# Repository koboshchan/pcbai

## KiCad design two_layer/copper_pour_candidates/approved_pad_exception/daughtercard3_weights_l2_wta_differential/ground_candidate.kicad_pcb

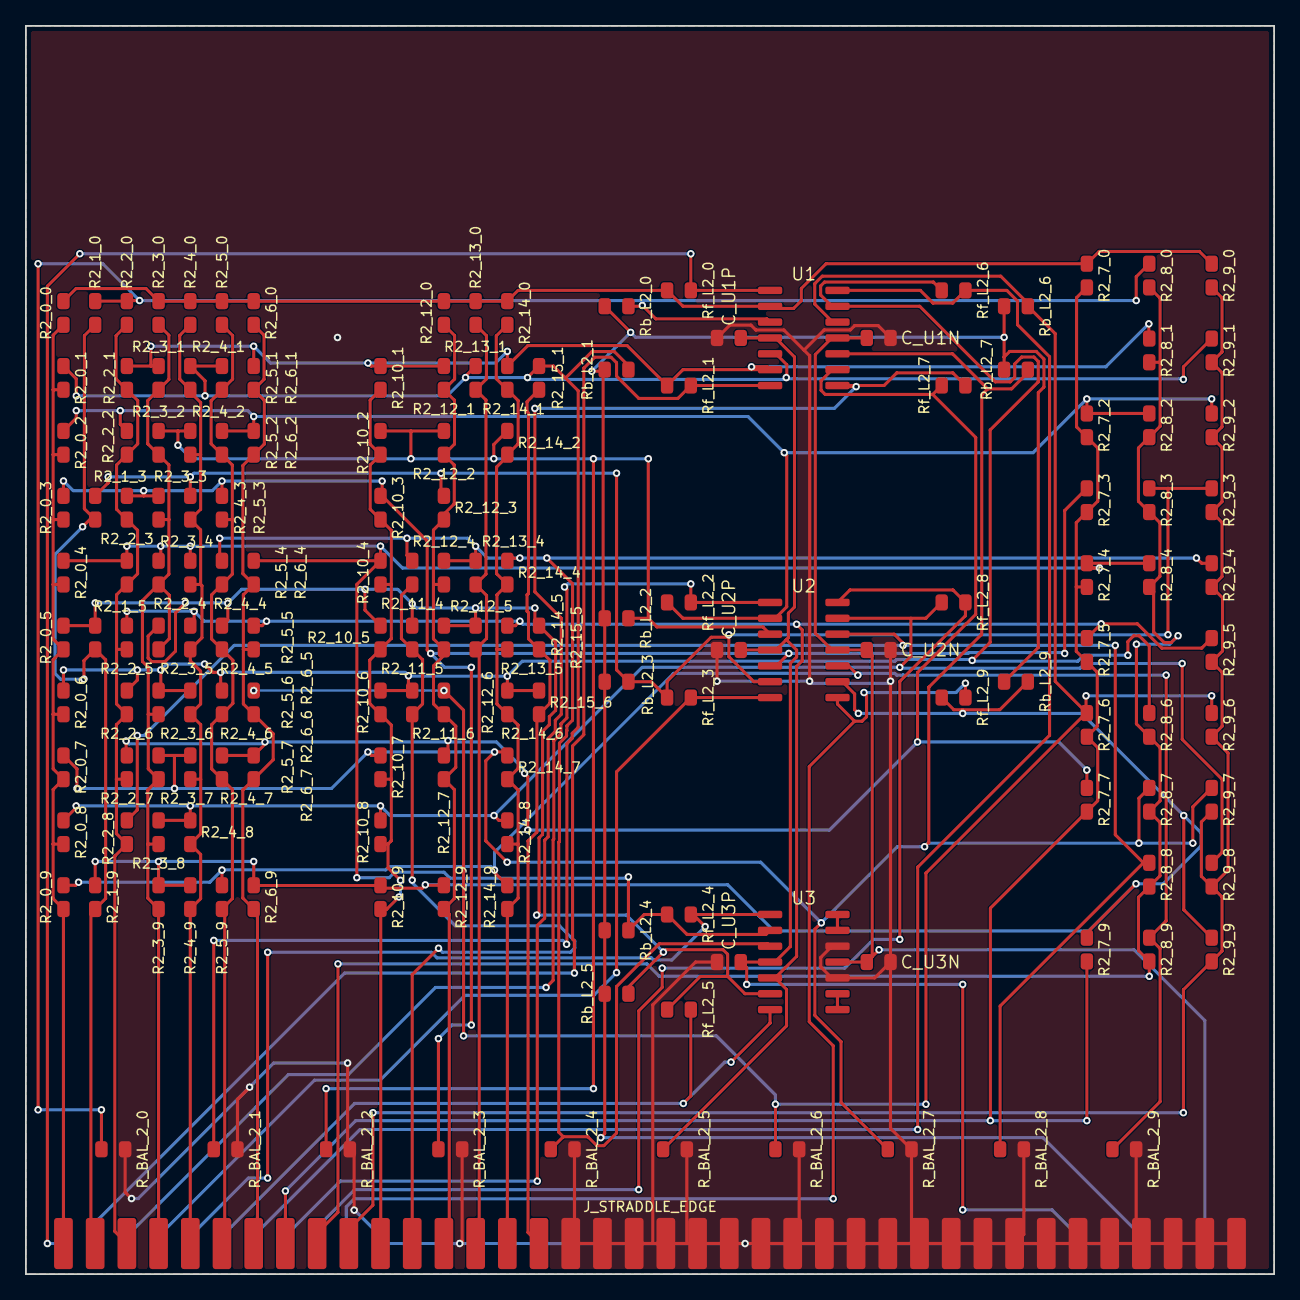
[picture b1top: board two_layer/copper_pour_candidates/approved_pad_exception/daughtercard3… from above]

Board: 2 copper layers, 100.0 x 100.0 mm, 163 parts (0 on the bottom side), 52 nets.

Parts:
C_U1N, C_U1P, C_U2N, C_U2P, C_U3N, C_U3P: 0.1uF; C_0805_2012Metric
J_STRADDLE_EDGE: PinHeader_2x38_Straddle; PinHeader_2x38_Straddle_P2.54mm
R2_0_0, R2_3_2, R2_8_3, R2_9_1, R2_10_6: 91k; R_0805_2012Metric
R2_0_1, R2_3_0, R2_6_5, R2_7_4, R2_9_0, R2_14_1: 100k; R_0805_2012Metric
R2_0_2: 1.6M; R_0805_2012Metric
R2_0_3, R2_1_3, R2_5_4, R2_6_2, R2_7_6, R2_10_5, R2_10_8, R2_13_0, R2_14_0: 220k; R_0805_2012Metric
R2_0_4, R2_2_7, R2_5_3, R2_7_3, R2_8_6, R2_9_3, R2_13_5: 270k; R_0805_2012Metric
R2_0_5, R2_0_6, R2_5_0: 56k; R_0805_2012Metric
R2_0_7, R2_3_5: 470k; R_0805_2012Metric
R2_0_8, R2_1_9, R2_5_5, R2_5_9, R2_9_2, R2_9_4, R2_9_8, R2_10_7, R2_11_4, R2_11_6, R2_12_6: 180k; R_0805_2012Metric
R2_0_9, R2_2_2, R2_4_5, R2_4_6, R2_8_9, R2_12_5, R2_14_9: 300k; R_0805_2012Metric
R2_1_0, R2_2_3, R2_2_4, R2_8_0, R2_10_3, R2_11_5, R2_14_7, R2_15_5: 240k; R_0805_2012Metric
R2_1_5, R2_5_1: 82k; R_0805_2012Metric
R2_2_0, R2_10_9, R2_14_8: 110k; R_0805_2012Metric
R2_2_1: 51k; R_0805_2012Metric
R2_2_5, R2_3_3, R2_3_7, R2_15_6: 360k; R_0805_2012Metric
R2_2_6, R2_4_9: 430k; R_0805_2012Metric
R2_2_8: 5.1M; R_0805_2012Metric
R2_3_1, R2_6_9, R2_7_7, R2_9_9, R2_10_2, R2_13_4: 150k; R_0805_2012Metric
R2_3_4, R2_3_9, R2_5_2, R2_14_4: 130k; R_0805_2012Metric
R2_3_6, R2_5_6, R2_6_4, R2_7_2, R2_7_5, R2_10_1: 68k; R_0805_2012Metric
R2_3_8, R2_5_7, R2_6_0, R2_6_6, R2_8_2, R2_12_1, R2_12_4, R2_14_6: 200k; R_0805_2012Metric
R2_4_0, R2_9_5: 1M; R_0805_2012Metric
R2_4_1, R2_4_4, R2_8_8: 120k; R_0805_2012Metric
R2_4_2: 680k; R_0805_2012Metric
R2_4_3, R2_14_2: 750k; R_0805_2012Metric
R2_4_7, R2_12_3: 390k; R_0805_2012Metric
R2_4_8: 62k; R_0805_2012Metric
R2_6_1, R2_12_7: 43k; R_0805_2012Metric
R2_6_7, R2_8_7: 330k; R_0805_2012Metric
R2_7_0, R2_7_9: 75k; R_0805_2012Metric
R2_8_1, R2_12_9, R2_15_1: 160k; R_0805_2012Metric
R2_8_4, R2_9_6, R2_9_7: 620k; R_0805_2012Metric
R2_10_4: 33k; R_0805_2012Metric
R2_12_0: 510k; R_0805_2012Metric
R2_12_2: 1.1M; R_0805_2012Metric
R2_13_1: 820k; R_0805_2012Metric
R2_14_5: 2.7M; R_0805_2012Metric
R_BAL_2_0: 14.7k; R_0805_2012Metric
R_BAL_2_1: 24.9k; R_0805_2012Metric
R_BAL_2_2: 35.7k; R_0805_2012Metric
R_BAL_2_3: 61.9k; R_0805_2012Metric
R_BAL_2_4: 17.4k; R_0805_2012Metric
R_BAL_2_5: 28k; R_0805_2012Metric
R_BAL_2_6: 14.3k; R_0805_2012Metric
R_BAL_2_7: 34k; R_0805_2012Metric
R_BAL_2_8: 21k; R_0805_2012Metric
R_BAL_2_9: 18.2k; R_0805_2012Metric
Rb_L2_0: 270k; R_0805_2012Metric
Rb_L2_1, Rb_L2_3: 160k; R_0805_2012Metric
Rb_L2_2, Rb_L2_4: 560k; R_0805_2012Metric
Rb_L2_5: 2M; R_0805_2012Metric
Rb_L2_6: 240k; R_0805_2012Metric
Rb_L2_7: 3.9M; R_0805_2012Metric
Rb_L2_9: 360k; R_0805_2012Metric
Rf_L2_0, Rf_L2_1, Rf_L2_2, Rf_L2_3, Rf_L2_4, Rf_L2_5, Rf_L2_6, Rf_L2_7, Rf_L2_8, Rf_L2_9: 100k; R_0805_2012Metric
U1, U2, U3: TL074; SOIC-14_3.9x8.7mm_P1.27mm

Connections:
+5V_REF: J_STRADDLE_EDGE.B35, Rb_L2_0.1, Rb_L2_1.1, Rb_L2_2.1, Rb_L2_3.1, Rb_L2_4.1, Rb_L2_5.1, Rb_L2_6.1, Rb_L2_7.1, Rb_L2_9.1
+15V: C_U1P.2, C_U2P.2, C_U3P.2, J_STRADDLE_EDGE.B33, J_STRADDLE_EDGE.B34, U1.4, U2.4, U3.4
-15V: C_U1N.1, C_U2N.1, C_U3N.1, J_STRADDLE_EDGE.B37, J_STRADDLE_EDGE.B38, U1.11, U2.11, U3.11
ACT_0: J_STRADDLE_EDGE.A1, R2_0_0.1, R2_0_1.1, R2_0_2.1, R2_0_3.1, R2_0_4.1, R2_0_5.1, R2_0_6.1, R2_0_7.1, R2_0_8.1, R2_0_9.1
ACT_1: J_STRADDLE_EDGE.A2, R2_1_0.1, R2_1_3.1, R2_1_5.1, R2_1_9.1
ACT_2: J_STRADDLE_EDGE.A3, R2_2_0.1, R2_2_1.1, R2_2_2.1, R2_2_3.1, R2_2_4.1, R2_2_5.1, R2_2_6.1, R2_2_7.1, R2_2_8.1
ACT_3: J_STRADDLE_EDGE.A4, R2_3_0.1, R2_3_1.1, R2_3_2.1, R2_3_3.1, R2_3_4.1, R2_3_5.1, R2_3_6.1, R2_3_7.1, R2_3_8.1, R2_3_9.1
ACT_4: J_STRADDLE_EDGE.A5, R2_4_0.1, R2_4_1.1, R2_4_2.1, R2_4_3.1, R2_4_4.1, R2_4_5.1, R2_4_6.1, R2_4_7.1, R2_4_8.1, R2_4_9.1
ACT_5: J_STRADDLE_EDGE.A6, R2_5_0.1, R2_5_1.1, R2_5_2.1, R2_5_3.1, R2_5_4.1, R2_5_5.1, R2_5_6.1, R2_5_7.1, R2_5_9.1
ACT_6: J_STRADDLE_EDGE.A7, R2_6_0.1, R2_6_1.1, R2_6_2.1, R2_6_4.1, R2_6_5.1, R2_6_6.1, R2_6_7.1, R2_6_9.1
ACT_7: J_STRADDLE_EDGE.A8, R2_7_0.1, R2_7_2.1, R2_7_3.1, R2_7_4.1, R2_7_5.1, R2_7_6.1, R2_7_7.1, R2_7_9.1
ACT_8: J_STRADDLE_EDGE.A9, R2_8_0.1, R2_8_1.1, R2_8_2.1, R2_8_3.1, R2_8_4.1, R2_8_6.1, R2_8_7.1, R2_8_8.1, R2_8_9.1
ACT_9: J_STRADDLE_EDGE.A10, R2_9_0.1, R2_9_1.1, R2_9_2.1, R2_9_3.1, R2_9_4.1, R2_9_5.1, R2_9_6.1, R2_9_7.1, R2_9_8.1, R2_9_9.1
ACT_10: J_STRADDLE_EDGE.A11, R2_10_1.1, R2_10_2.1, R2_10_3.1, R2_10_4.1, R2_10_5.1, R2_10_6.1, R2_10_7.1, R2_10_8.1, R2_10_9.1
ACT_11: J_STRADDLE_EDGE.A12, R2_11_4.1, R2_11_5.1, R2_11_6.1
ACT_12: J_STRADDLE_EDGE.A13, R2_12_0.1, R2_12_1.1, R2_12_2.1, R2_12_3.1, R2_12_4.1, R2_12_5.1, R2_12_6.1, R2_12_7.1, R2_12_9.1
ACT_13: J_STRADDLE_EDGE.A14, R2_13_0.1, R2_13_1.1, R2_13_4.1, R2_13_5.1
ACT_14: J_STRADDLE_EDGE.A15, R2_14_0.1, R2_14_1.1, R2_14_2.1, R2_14_4.1, R2_14_5.1, R2_14_6.1, R2_14_7.1, R2_14_8.1, R2_14_9.1
ACT_15: J_STRADDLE_EDGE.A16, R2_15_1.1, R2_15_5.1, R2_15_6.1
GND: C_U1N.2, C_U1P.1, C_U2N.2, C_U2P.1, C_U3N.2, C_U3P.1, J_STRADDLE_EDGE.A17, J_STRADDLE_EDGE.A18, J_STRADDLE_EDGE.A19, J_STRADDLE_EDGE.A20, J_STRADDLE_EDGE.A21, J_STRADDLE_EDGE.A22, J_STRADDLE_EDGE.A23, J_STRADDLE_EDGE.A24, J_STRADDLE_EDGE.A25, J_STRADDLE_EDGE.A26, J_STRADDLE_EDGE.A27, J_STRADDLE_EDGE.A28, J_STRADDLE_EDGE.A29, J_STRADDLE_EDGE.A30, J_STRADDLE_EDGE.A31, J_STRADDLE_EDGE.A32, J_STRADDLE_EDGE.A33, J_STRADDLE_EDGE.A34, J_STRADDLE_EDGE.A35, J_STRADDLE_EDGE.A36, J_STRADDLE_EDGE.A37, J_STRADDLE_EDGE.A38, J_STRADDLE_EDGE.B11, J_STRADDLE_EDGE.B12, J_STRADDLE_EDGE.B13, J_STRADDLE_EDGE.B14, J_STRADDLE_EDGE.B15, J_STRADDLE_EDGE.B16, J_STRADDLE_EDGE.B17, J_STRADDLE_EDGE.B18, J_STRADDLE_EDGE.B19, J_STRADDLE_EDGE.B20, J_STRADDLE_EDGE.B21, J_STRADDLE_EDGE.B22, J_STRADDLE_EDGE.B23, J_STRADDLE_EDGE.B24, J_STRADDLE_EDGE.B25, J_STRADDLE_EDGE.B26, J_STRADDLE_EDGE.B27, J_STRADDLE_EDGE.B28, J_STRADDLE_EDGE.B29, J_STRADDLE_EDGE.B30, J_STRADDLE_EDGE.B31, J_STRADDLE_EDGE.B32, R_BAL_2_0.2, R_BAL_2_1.2, R_BAL_2_2.2, R_BAL_2_3.2, R_BAL_2_4.2, R_BAL_2_5.2, R_BAL_2_6.2, R_BAL_2_7.2, R_BAL_2_8.2, R_BAL_2_9.2, U3.10, U3.12
INV_L2_0: R2_0_0.2, R2_3_0.2, R2_4_0.2, R2_5_0.2, R2_6_0.2, R2_7_0.2, R2_9_0.2, R2_12_0.2, R2_13_0.2, R2_14_0.2, Rf_L2_0.1, U1.2
INV_L2_1: R2_2_1.2, R2_3_1.2, R2_6_1.2, R2_8_1.2, R2_10_1.2, R2_12_1.2, R2_14_1.2, Rf_L2_1.1, U1.6
INV_L2_2: R2_0_2.2, R2_2_2.2, R2_5_2.2, R2_6_2.2, R2_7_2.2, R2_8_2.2, R2_9_2.2, Rf_L2_2.1, U2.2
INV_L2_3: R2_1_3.2, R2_4_3.2, R2_8_3.2, R2_9_3.2, R2_12_3.2, Rb_L2_3.2, Rf_L2_3.1, U2.6
INV_L2_4: R2_0_4.2, R2_2_4.2, R2_3_4.2, R2_4_4.2, R2_6_4.2, R2_7_4.2, R2_8_4.2, R2_10_4.2, Rb_L2_4.2, Rf_L2_4.1, U3.2
INV_L2_5: R2_0_5.2, R2_1_5.2, R2_3_5.2, R2_5_5.2, R2_10_5.2, R2_11_5.2, R2_12_5.2, R2_13_5.2, R2_15_5.2, Rb_L2_5.2, Rf_L2_5.1, U3.6
INV_L2_6: R2_0_6.2, R2_2_6.2, R2_3_6.2, R2_4_6.2, R2_5_6.2, R2_8_6.2, R2_10_6.2, R2_11_6.2, R2_14_6.2, R2_15_6.2, Rf_L2_6.1, U1.13
INV_L2_7: R2_2_7.2, R2_5_7.2, R2_6_7.2, R2_7_7.2, R2_12_7.2, Rf_L2_7.1, U1.9
INV_L2_8: R2_0_8.2, R2_3_8.2, R2_4_8.2, R2_9_8.2, R2_10_8.2, R2_14_8.2, Rf_L2_8.1, U2.13
INV_L2_9: R2_1_9.2, R2_3_9.2, R2_4_9.2, R2_6_9.2, R2_7_9.2, R2_9_9.2, R2_10_9.2, R2_12_9.2, Rb_L2_9.2, Rf_L2_9.1, U2.9
NC_U3_8: U3.8, U3.9
NC_U3_14: U3.13, U3.14
POS_L2_0: R2_1_0.2, R2_2_0.2, R2_8_0.2, R_BAL_2_0.1, Rb_L2_0.2, U1.3
POS_L2_1: R2_0_1.2, R2_4_1.2, R2_5_1.2, R2_9_1.2, R2_13_1.2, R2_15_1.2, R_BAL_2_1.1, Rb_L2_1.2, U1.5
POS_L2_2: R2_3_2.2, R2_4_2.2, R2_10_2.2, R2_12_2.2, R2_14_2.2, R_BAL_2_2.1, Rb_L2_2.2, U2.3
POS_L2_3: R2_0_3.2, R2_2_3.2, R2_3_3.2, R2_5_3.2, R2_7_3.2, R2_10_3.2, R_BAL_2_3.1, U2.5
POS_L2_4: R2_5_4.2, R2_9_4.2, R2_11_4.2, R2_12_4.2, R2_13_4.2, R2_14_4.2, R_BAL_2_4.1, U3.3
POS_L2_5: R2_2_5.2, R2_4_5.2, R2_6_5.2, R2_7_5.2, R2_9_5.2, R2_14_5.2, R_BAL_2_5.1, U3.5
POS_L2_6: R2_6_6.2, R2_7_6.2, R2_9_6.2, R2_12_6.2, R_BAL_2_6.1, Rb_L2_6.2, U1.12
POS_L2_7: R2_0_7.2, R2_3_7.2, R2_4_7.2, R2_8_7.2, R2_9_7.2, R2_10_7.2, R2_14_7.2, R_BAL_2_7.1, Rb_L2_7.2, U1.10
POS_L2_8: R2_2_8.2, R2_8_8.2, R_BAL_2_8.1, U2.12
POS_L2_9: R2_0_9.2, R2_5_9.2, R2_8_9.2, R2_14_9.2, R_BAL_2_9.1, U2.10
SCORE_0: J_STRADDLE_EDGE.B1, Rf_L2_0.2, U1.1
SCORE_1: J_STRADDLE_EDGE.B2, Rf_L2_1.2, U1.7
SCORE_2: J_STRADDLE_EDGE.B3, Rf_L2_2.2, U2.1
SCORE_3: J_STRADDLE_EDGE.B4, Rf_L2_3.2, U2.7
SCORE_4: J_STRADDLE_EDGE.B5, Rf_L2_4.2, U3.1
SCORE_5: J_STRADDLE_EDGE.B6, Rf_L2_5.2, U3.7
SCORE_6: J_STRADDLE_EDGE.B7, Rf_L2_6.2, U1.14
SCORE_7: J_STRADDLE_EDGE.B8, Rf_L2_7.2, U1.8
SCORE_8: J_STRADDLE_EDGE.B9, Rf_L2_8.2, U2.14
SCORE_9: J_STRADDLE_EDGE.B10, Rf_L2_9.2, U2.8

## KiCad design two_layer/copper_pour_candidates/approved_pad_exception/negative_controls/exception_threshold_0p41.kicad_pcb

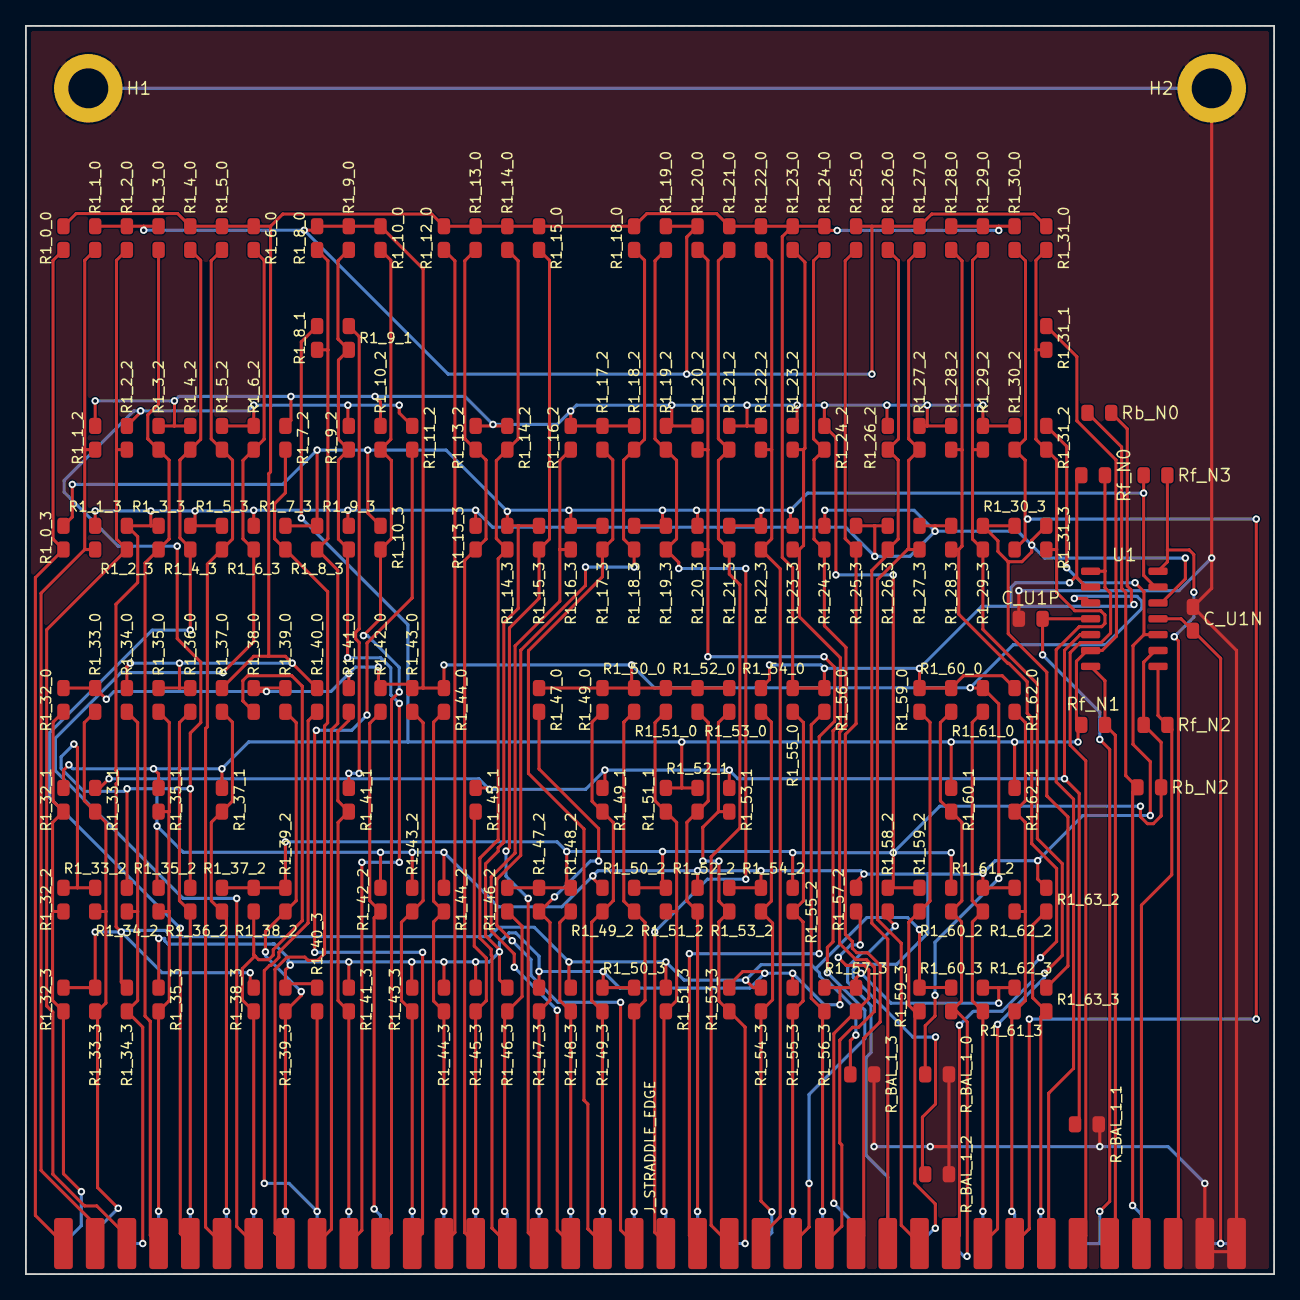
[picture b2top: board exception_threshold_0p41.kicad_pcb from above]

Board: 2 copper layers, 100.0 x 100.0 mm, 197 parts (0 on the bottom side), 80 nets.

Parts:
C_U1N, C_U1P: 0.1uF; C_0805_2012Metric
H1, H2: MountingHole; MountingHole_3.2mm_M3_Pad
J_STRADDLE_EDGE: PinHeader_2x38_Straddle; PinHeader_2x38_Straddle_P2.54mm
R1_0_0: 30k; R_0805_2012Metric
R1_0_3, R1_16_3, R1_23_2: 47k; R_0805_2012Metric
R1_1_0, R1_10_0, R1_26_0, R1_34_3, R1_42_0, R1_43_0, R1_45_1, R1_53_2, R1_58_2: 390k; R_0805_2012Metric
R1_1_2, R1_5_2, R1_33_1, R1_39_0, R1_41_1, R1_47_2, R1_47_3, R1_49_1, R1_62_3: 110k; R_0805_2012Metric
R1_1_3, R1_22_3, R1_45_3: 2M; R_0805_2012Metric
R1_2_0, R1_3_3, R1_12_0, R1_16_2, R1_18_2, R1_27_0: 160k; R_0805_2012Metric
R1_2_2: 1.5M; R_0805_2012Metric
R1_2_3, R1_21_0, R1_62_1: 120k; R_0805_2012Metric
R1_3_0, R1_7_3, R1_20_2, R1_23_0, R1_31_3, R1_33_2, R1_34_2: 180k; R_0805_2012Metric
R1_3_2, R1_11_2, R1_28_2, R1_35_0, R1_50_2, R1_51_1: 680k; R_0805_2012Metric
R1_4_0, R1_8_3, R1_19_3, R1_22_0, R1_60_1, R1_61_2: 130k; R_0805_2012Metric
R1_4_2, R1_40_0: 510k; R_0805_2012Metric
R1_4_3, R1_7_2, R1_15_0, R1_24_0, R1_26_3, R1_27_3, R1_39_3, R1_42_2: 150k; R_0805_2012Metric
R1_5_0, R1_8_0, R1_9_1, R1_13_2, R1_32_0, R1_37_2, R1_59_0: 360k; R_0805_2012Metric
R1_5_3, R1_9_2, R1_24_2, R1_29_0, R1_41_3, R1_48_2, R1_49_0, R1_61_0: 240k; R_0805_2012Metric
R1_6_0, R1_14_0, R1_26_2, R1_36_2, R1_49_2, R1_54_2: 270k; R_0805_2012Metric
R1_6_2, R1_9_0, R1_29_2, R1_35_1, R1_53_1, R1_55_2, R1_59_2, R1_59_3, R1_62_0: 200k; R_0805_2012Metric
R1_6_3, R1_20_0, R1_21_3, R1_25_0, R1_38_2, R1_54_0, R1_54_3: 430k; R_0805_2012Metric
R1_8_1, R1_19_0, R1_55_0: 82k; R_0805_2012Metric
R1_9_3, R1_36_0, R1_37_1, R1_48_3, R1_49_3, R1_51_3, R1_57_3: 470k; R_0805_2012Metric
R1_10_2, R1_23_3, R1_30_3, R1_51_0, R1_52_0, R1_53_0: 560k; R_0805_2012Metric
R1_10_3, R1_28_3, R1_31_0: 620k; R_0805_2012Metric
R1_13_0, R1_17_2, R1_19_2, R1_31_2, R1_35_2, R1_57_2, R1_60_2: 220k; R_0805_2012Metric
R1_13_3, R1_52_2: 3.3M; R_0805_2012Metric
R1_14_2, R1_27_2, R1_29_3, R1_30_2, R1_35_3, R1_38_0, R1_41_0, R1_44_2, R1_50_0, R1_51_2, R1_60_3, R1_61_3: 330k; R_0805_2012Metric
R1_14_3, R1_53_3, R1_60_0: 1.1M; R_0805_2012Metric
R1_15_3, R1_28_0, R1_38_3, R1_46_2: 300k; R_0805_2012Metric
R1_17_3, R1_63_2: 56k; R_0805_2012Metric
R1_18_0, R1_32_2, R1_50_3: 910k; R_0805_2012Metric
R1_18_3, R1_22_2, R1_32_1, R1_33_3, R1_43_2, R1_55_3: 91k; R_0805_2012Metric
R1_20_3: 2.2M; R_0805_2012Metric
R1_21_2, R1_62_2, R1_63_3: 100k; R_0805_2012Metric
R1_24_3, R1_25_3, R1_31_1, R1_39_2, R1_56_3: 75k; R_0805_2012Metric
R1_30_0: 1.6M; R_0805_2012Metric
R1_32_3: 27k; R_0805_2012Metric
R1_33_0, R1_46_3: 1M; R_0805_2012Metric
R1_34_0: 1.3M; R_0805_2012Metric
R1_37_0, R1_44_0, R1_52_1: 1.2M; R_0805_2012Metric
R1_40_3: 43k; R_0805_2012Metric
R1_43_3: 750k; R_0805_2012Metric
R1_44_3: 2.4M; R_0805_2012Metric
R1_47_0: 68k; R_0805_2012Metric
R1_56_0: 62k; R_0805_2012Metric
R_BAL_1_0: 18.2k; R_0805_2012Metric
R_BAL_1_1: 29.4k; R_0805_2012Metric
R_BAL_1_2: 14.7k; R_0805_2012Metric
R_BAL_1_3: 22.6k; R_0805_2012Metric
Rb_N0: 6.2M; R_0805_2012Metric
Rb_N2: 1.1M; R_0805_2012Metric
Rf_N0, Rf_N1, Rf_N2, Rf_N3: 100k; R_0805_2012Metric
U1: TL074; SOIC-14_3.9x8.7mm_P1.27mm

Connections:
+5V_REF: J_STRADDLE_EDGE.B35, Rb_N0.1, Rb_N2.1
+15V: C_U1P.2, J_STRADDLE_EDGE.B33, J_STRADDLE_EDGE.B34, U1.4
-15V: C_U1N.1, J_STRADDLE_EDGE.B37, J_STRADDLE_EDGE.B38, U1.11
GND: C_U1N.2, C_U1P.1, H1.1, H2.1, J_STRADDLE_EDGE.A37, J_STRADDLE_EDGE.A38, R_BAL_1_0.2, R_BAL_1_1.2, R_BAL_1_2.2, R_BAL_1_3.2
INV_N0: R1_0_0.2, R1_4_0.2, R1_5_0.2, R1_6_0.2, R1_12_0.2, R1_13_0.2, R1_14_0.2, R1_15_0.2, R1_18_0.2, R1_21_0.2, R1_22_0.2, R1_23_0.2, R1_24_0.2, R1_28_0.2, R1_29_0.2, R1_30_0.2, R1_34_0.2, R1_35_0.2, R1_36_0.2, R1_37_0.2, R1_40_0.2, R1_54_0.2, R1_55_0.2, R1_56_0.2, R1_59_0.2, R1_60_0.2, R1_62_0.2, Rb_N0.2, Rf_N0.1, U1.2
INV_N1: R1_8_1.2, R1_31_1.2, R1_32_1.2, R1_35_1.2, R1_37_1.2, R1_51_1.2, R1_52_1.2, R1_60_1.2, R1_62_1.2, Rf_N1.1, U1.6
INV_N2: R1_1_2.2, R1_3_2.2, R1_4_2.2, R1_7_2.2, R1_10_2.2, R1_13_2.2, R1_14_2.2, R1_16_2.2, R1_17_2.2, R1_18_2.2, R1_19_2.2, R1_20_2.2, R1_21_2.2, R1_22_2.2, R1_23_2.2, R1_24_2.2, R1_26_2.2, R1_27_2.2, R1_28_2.2, R1_29_2.2, R1_30_2.2, R1_37_2.2, R1_38_2.2, R1_39_2.2, R1_46_2.2, R1_47_2.2, R1_48_2.2, R1_50_2.2, R1_51_2.2, R1_55_2.2, R1_58_2.2, R1_59_2.2, R1_60_2.2, Rb_N2.2, Rf_N2.1, U1.9
INV_N3: R1_0_3.2, R1_7_3.2, R1_8_3.2, R1_10_3.2, R1_14_3.2, R1_15_3.2, R1_16_3.2, R1_17_3.2, R1_18_3.2, R1_19_3.2, R1_20_3.2, R1_21_3.2, R1_22_3.2, R1_23_3.2, R1_35_3.2, R1_39_3.2, R1_40_3.2, R1_41_3.2, R1_43_3.2, R1_44_3.2, R1_45_3.2, R1_46_3.2, R1_47_3.2, R1_49_3.2, R1_50_3.2, R1_53_3.2, R1_55_3.2, R1_56_3.2, R1_57_3.2, R1_61_3.2, R1_62_3.2, Rf_N3.1, U1.13
IN_0: J_STRADDLE_EDGE.A1, R1_0_0.1, R1_0_3.1
IN_1: J_STRADDLE_EDGE.A2, R1_1_0.1, R1_1_2.1, R1_1_3.1
IN_2: J_STRADDLE_EDGE.A3, R1_2_0.1, R1_2_2.1, R1_2_3.1
IN_3: J_STRADDLE_EDGE.A4, R1_3_0.1, R1_3_2.1, R1_3_3.1
IN_4: J_STRADDLE_EDGE.A5, R1_4_0.1, R1_4_2.1, R1_4_3.1
IN_5: J_STRADDLE_EDGE.A6, R1_5_0.1, R1_5_2.1, R1_5_3.1
IN_6: J_STRADDLE_EDGE.A7, R1_6_0.1, R1_6_2.1, R1_6_3.1
IN_7: J_STRADDLE_EDGE.A8, R1_7_2.1, R1_7_3.1
IN_8: J_STRADDLE_EDGE.A9, R1_8_0.1, R1_8_1.1, R1_8_3.1
IN_9: J_STRADDLE_EDGE.A10, R1_9_0.1, R1_9_1.1, R1_9_2.1, R1_9_3.1
IN_10: J_STRADDLE_EDGE.A11, R1_10_0.1, R1_10_2.1, R1_10_3.1
IN_11: J_STRADDLE_EDGE.A12, R1_11_2.1
IN_12: J_STRADDLE_EDGE.A13, R1_12_0.1
IN_13: J_STRADDLE_EDGE.A14, R1_13_0.1, R1_13_2.1, R1_13_3.1
IN_14: J_STRADDLE_EDGE.A15, R1_14_0.1, R1_14_2.1, R1_14_3.1
IN_15: J_STRADDLE_EDGE.A16, R1_15_0.1, R1_15_3.1
IN_16: J_STRADDLE_EDGE.A17, R1_16_2.1, R1_16_3.1
IN_17: J_STRADDLE_EDGE.A18, R1_17_2.1, R1_17_3.1
IN_18: J_STRADDLE_EDGE.A19, R1_18_0.1, R1_18_2.1, R1_18_3.1
IN_19: J_STRADDLE_EDGE.A20, R1_19_0.1, R1_19_2.1, R1_19_3.1
IN_20: J_STRADDLE_EDGE.A21, R1_20_0.1, R1_20_2.1, R1_20_3.1
IN_21: J_STRADDLE_EDGE.A22, R1_21_0.1, R1_21_2.1, R1_21_3.1
IN_22: J_STRADDLE_EDGE.A23, R1_22_0.1, R1_22_2.1, R1_22_3.1
IN_23: J_STRADDLE_EDGE.A24, R1_23_0.1, R1_23_2.1, R1_23_3.1
IN_24: J_STRADDLE_EDGE.A25, R1_24_0.1, R1_24_2.1, R1_24_3.1
IN_25: J_STRADDLE_EDGE.A26, R1_25_0.1, R1_25_3.1
IN_26: J_STRADDLE_EDGE.A27, R1_26_0.1, R1_26_2.1, R1_26_3.1
IN_27: J_STRADDLE_EDGE.A28, R1_27_0.1, R1_27_2.1, R1_27_3.1
IN_28: J_STRADDLE_EDGE.A29, R1_28_0.1, R1_28_2.1, R1_28_3.1
IN_29: J_STRADDLE_EDGE.A30, R1_29_0.1, R1_29_2.1, R1_29_3.1
IN_30: J_STRADDLE_EDGE.A31, R1_30_0.1, R1_30_2.1, R1_30_3.1
IN_31: J_STRADDLE_EDGE.A32, R1_31_0.1, R1_31_1.1, R1_31_2.1, R1_31_3.1
IN_32: J_STRADDLE_EDGE.B1, R1_32_0.1, R1_32_1.1, R1_32_2.1, R1_32_3.1
IN_33: J_STRADDLE_EDGE.B2, R1_33_0.1, R1_33_1.1, R1_33_2.1, R1_33_3.1
IN_34: J_STRADDLE_EDGE.B3, R1_34_0.1, R1_34_2.1, R1_34_3.1
IN_35: J_STRADDLE_EDGE.B4, R1_35_0.1, R1_35_1.1, R1_35_2.1, R1_35_3.1
IN_36: J_STRADDLE_EDGE.B5, R1_36_0.1, R1_36_2.1
IN_37: J_STRADDLE_EDGE.B6, R1_37_0.1, R1_37_1.1, R1_37_2.1
IN_38: J_STRADDLE_EDGE.B7, R1_38_0.1, R1_38_2.1, R1_38_3.1
IN_39: J_STRADDLE_EDGE.B8, R1_39_0.1, R1_39_2.1, R1_39_3.1
IN_40: J_STRADDLE_EDGE.B9, R1_40_0.1, R1_40_3.1
IN_41: J_STRADDLE_EDGE.B10, R1_41_0.1, R1_41_1.1, R1_41_3.1
IN_42: J_STRADDLE_EDGE.B11, R1_42_0.1, R1_42_2.1
IN_43: J_STRADDLE_EDGE.B12, R1_43_0.1, R1_43_2.1, R1_43_3.1
IN_44: J_STRADDLE_EDGE.B13, R1_44_0.1, R1_44_2.1, R1_44_3.1
IN_45: J_STRADDLE_EDGE.B14, R1_45_1.1, R1_45_3.1
IN_46: J_STRADDLE_EDGE.B15, R1_46_2.1, R1_46_3.1
IN_47: J_STRADDLE_EDGE.B16, R1_47_0.1, R1_47_2.1, R1_47_3.1
IN_48: J_STRADDLE_EDGE.B17, R1_48_2.1, R1_48_3.1
IN_49: J_STRADDLE_EDGE.B18, R1_49_0.1, R1_49_1.1, R1_49_2.1, R1_49_3.1
IN_50: J_STRADDLE_EDGE.B19, R1_50_0.1, R1_50_2.1, R1_50_3.1
IN_51: J_STRADDLE_EDGE.B20, R1_51_0.1, R1_51_1.1, R1_51_2.1, R1_51_3.1
IN_52: J_STRADDLE_EDGE.B21, R1_52_0.1, R1_52_1.1, R1_52_2.1
IN_53: J_STRADDLE_EDGE.B22, R1_53_0.1, R1_53_1.1, R1_53_2.1, R1_53_3.1
IN_54: J_STRADDLE_EDGE.B23, R1_54_0.1, R1_54_2.1, R1_54_3.1
IN_55: J_STRADDLE_EDGE.B24, R1_55_0.1, R1_55_2.1, R1_55_3.1
IN_56: J_STRADDLE_EDGE.B25, R1_56_0.1, R1_56_3.1
IN_57: J_STRADDLE_EDGE.B26, R1_57_2.1, R1_57_3.1
IN_58: J_STRADDLE_EDGE.B27, R1_58_2.1
IN_59: J_STRADDLE_EDGE.B28, R1_59_0.1, R1_59_2.1, R1_59_3.1
IN_60: J_STRADDLE_EDGE.B29, R1_60_0.1, R1_60_1.1, R1_60_2.1, R1_60_3.1
IN_61: J_STRADDLE_EDGE.B30, R1_61_0.1, R1_61_2.1, R1_61_3.1
IN_62: J_STRADDLE_EDGE.B31, R1_62_0.1, R1_62_1.1, R1_62_2.1, R1_62_3.1
IN_63: J_STRADDLE_EDGE.B32, R1_63_2.1, R1_63_3.1
POS_N0: R1_1_0.2, R1_2_0.2, R1_3_0.2, R1_8_0.2, R1_9_0.2, R1_10_0.2, R1_19_0.2, R1_20_0.2, R1_25_0.2, R1_26_0.2, R1_27_0.2, R1_31_0.2, R1_32_0.2, R1_33_0.2, R1_38_0.2, R1_39_0.2, R1_41_0.2, R1_42_0.2, R1_43_0.2, R1_44_0.2, R1_47_0.2, R1_49_0.2, R1_50_0.2, R1_51_0.2, R1_52_0.2, R1_53_0.2, R1_61_0.2, R_BAL_1_0.1, U1.3
POS_N1: R1_9_1.2, R1_33_1.2, R1_41_1.2, R1_45_1.2, R1_49_1.2, R1_53_1.2, R_BAL_1_1.1, U1.5
POS_N2: R1_2_2.2, R1_5_2.2, R1_6_2.2, R1_9_2.2, R1_11_2.2, R1_31_2.2, R1_32_2.2, R1_33_2.2, R1_34_2.2, R1_35_2.2, R1_36_2.2, R1_42_2.2, R1_43_2.2, R1_44_2.2, R1_49_2.2, R1_52_2.2, R1_53_2.2, R1_54_2.2, R1_57_2.2, R1_61_2.2, R1_62_2.2, R1_63_2.2, R_BAL_1_2.1, U1.10
POS_N3: R1_1_3.2, R1_2_3.2, R1_3_3.2, R1_4_3.2, R1_5_3.2, R1_6_3.2, R1_9_3.2, R1_13_3.2, R1_24_3.2, R1_25_3.2, R1_26_3.2, R1_27_3.2, R1_28_3.2, R1_29_3.2, R1_30_3.2, R1_31_3.2, R1_32_3.2, R1_33_3.2, R1_34_3.2, R1_38_3.2, R1_48_3.2, R1_51_3.2, R1_54_3.2, R1_59_3.2, R1_60_3.2, R1_63_3.2, R_BAL_1_3.1, U1.12
V_SUM_0: J_STRADDLE_EDGE.A33, Rf_N0.2, U1.1
V_SUM_1: J_STRADDLE_EDGE.A34, Rf_N1.2, U1.7
V_SUM_2: J_STRADDLE_EDGE.A35, Rf_N2.2, U1.8
V_SUM_3: J_STRADDLE_EDGE.A36, Rf_N3.2, U1.14

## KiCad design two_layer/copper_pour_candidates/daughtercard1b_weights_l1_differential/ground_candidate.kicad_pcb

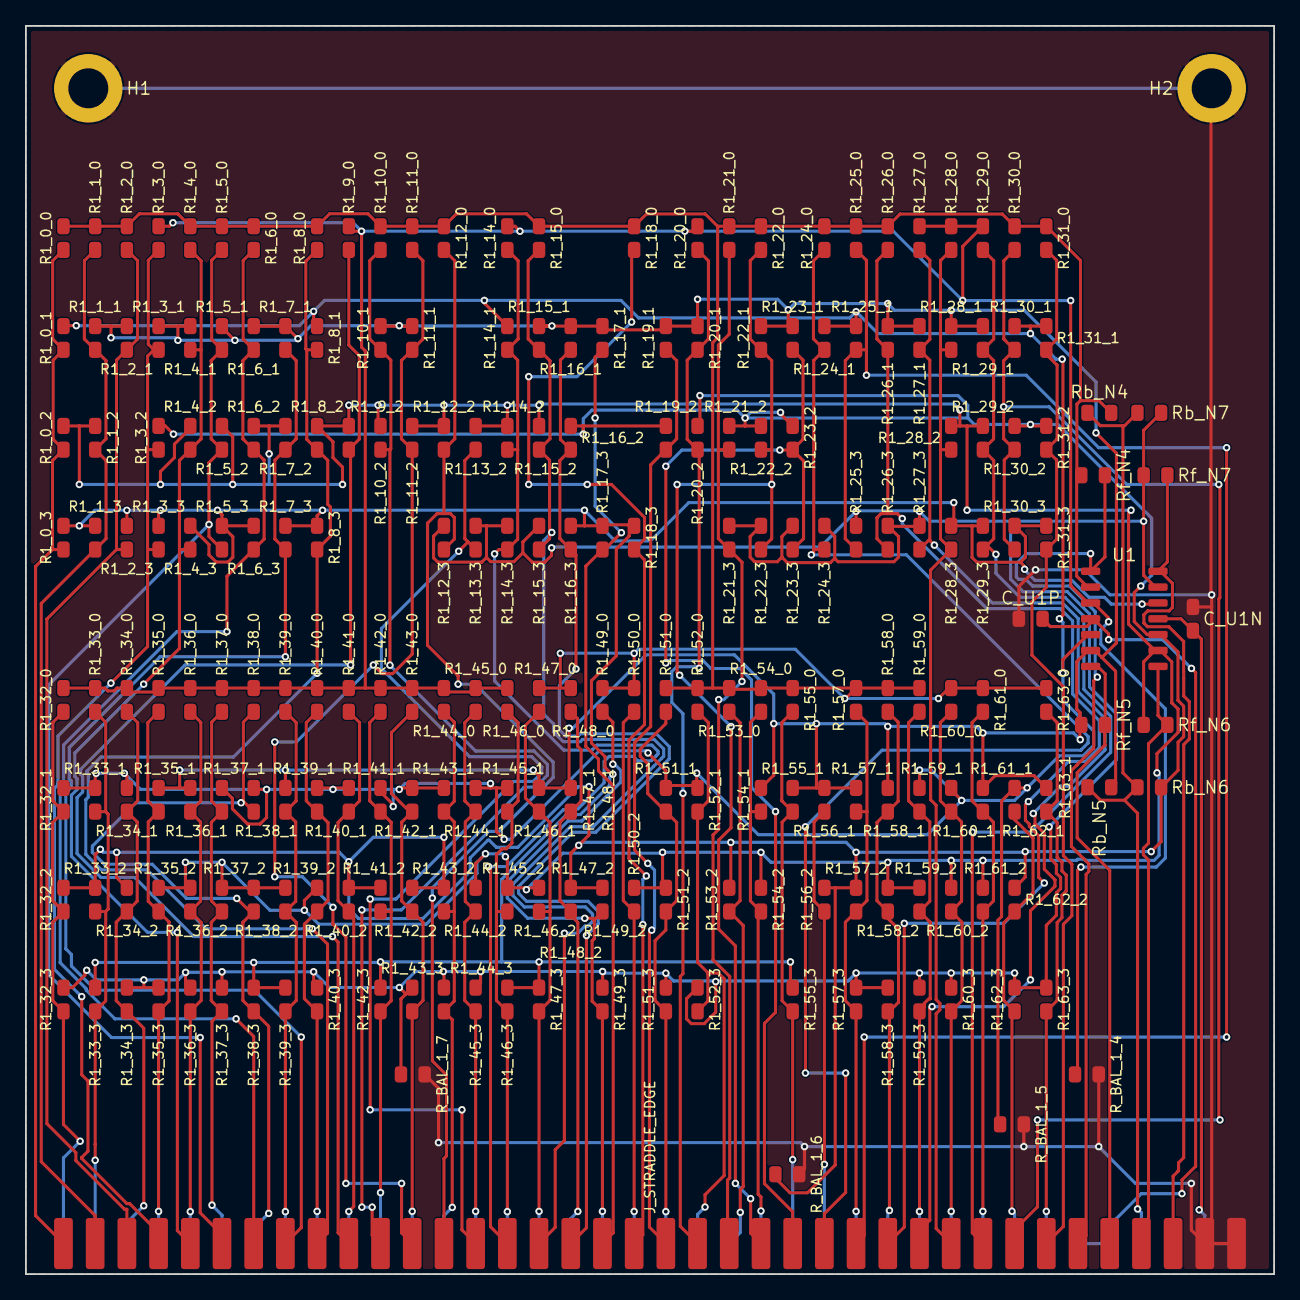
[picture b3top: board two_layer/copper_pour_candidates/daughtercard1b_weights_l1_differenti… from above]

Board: 2 copper layers, 100.0 x 100.0 mm, 236 parts (0 on the bottom side), 80 nets.

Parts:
C_U1N, C_U1P: 0.1uF; C_0805_2012Metric
H1, H2: MountingHole; MountingHole_3.2mm_M3_Pad
J_STRADDLE_EDGE: PinHeader_2x38_Straddle; PinHeader_2x38_Straddle_P2.54mm
R1_0_0, R1_23_2, R1_40_0, R1_41_0, R1_63_3: 51k; R_0805_2012Metric
R1_0_1, R1_5_3, R1_14_2, R1_38_0, R1_54_0: 130k; R_0805_2012Metric
R1_0_2, R1_0_3, R1_15_3, R1_21_2, R1_22_3, R1_63_1: 75k; R_0805_2012Metric
R1_1_0, R1_2_1, R1_13_2, R1_28_2, R1_35_0, R1_46_0, R1_47_2, R1_49_0, R1_51_1, R1_52_0, R1_57_0, R1_60_0, R1_60_2, R1_62_2: 200k; R_0805_2012Metric
R1_1_1, R1_3_1, R1_4_1, R1_8_3, R1_30_2, R1_36_0, R1_41_1, R1_48_1, R1_55_0: 150k; R_0805_2012Metric
R1_1_2, R1_20_0, R1_45_1, R1_45_2, R1_59_3: 240k; R_0805_2012Metric
R1_1_3, R1_23_1, R1_24_0, R1_32_1, R1_33_1, R1_48_0, R1_55_3: 91k; R_0805_2012Metric
R1_2_0, R1_29_1: 1.3M; R_0805_2012Metric
R1_2_3, R1_3_3, R1_11_0, R1_17_1, R1_18_0, R1_29_2, R1_38_1, R1_38_2, R1_39_0, R1_43_2, R1_59_0, R1_61_1: 330k; R_0805_2012Metric
R1_3_0, R1_11_2, R1_20_1, R1_30_1, R1_35_3: 430k; R_0805_2012Metric
R1_3_2, R1_22_0, R1_33_3, R1_34_2, R1_43_3, R1_46_3, R1_59_2: 680k; R_0805_2012Metric
R1_4_0, R1_9_0, R1_12_2, R1_21_3, R1_37_3, R1_58_1, R1_61_2: 270k; R_0805_2012Metric
R1_4_2, R1_4_3, R1_8_2, R1_24_3, R1_40_2, R1_40_3, R1_43_1: 110k; R_0805_2012Metric
R1_5_0, R1_14_0, R1_16_3, R1_25_3, R1_26_1, R1_42_3, R1_44_2, R1_45_3, R1_48_2, R1_49_2, R1_54_1: 510k; R_0805_2012Metric
R1_5_1, R1_11_1, R1_13_3, R1_24_1, R1_25_0, R1_29_0, R1_35_1, R1_39_1, R1_44_3, R1_45_0, R1_46_2, R1_53_2: 300k; R_0805_2012Metric
R1_5_2, R1_6_3, R1_20_2, R1_31_0, R1_32_0, R1_42_0, R1_42_1, R1_47_1, R1_47_3: 82k; R_0805_2012Metric
R1_6_0, R1_8_0, R1_31_1, R1_43_0: 100k; R_0805_2012Metric
R1_6_1, R1_10_1, R1_15_0, R1_15_1, R1_19_2, R1_27_0, R1_32_3, R1_55_1, R1_56_2, R1_57_3: 160k; R_0805_2012Metric
R1_6_2, R1_22_2: 56k; R_0805_2012Metric
R1_7_1, R1_15_2: 33k; R_0805_2012Metric
R1_7_2: 47k; R_0805_2012Metric
R1_7_3, R1_34_0, R1_35_2, R1_44_0: 390k; R_0805_2012Metric
R1_8_1, R1_22_1, R1_36_1, R1_37_0, R1_41_2, R1_42_2, R1_50_2, R1_54_2: 470k; R_0805_2012Metric
R1_9_2, R1_37_2, R1_62_1: 1M; R_0805_2012Metric
R1_10_0, R1_14_1, R1_58_2: 1.8M; R_0805_2012Metric
R1_10_2, R1_60_1: 1.6M; R_0805_2012Metric
R1_12_0, R1_21_0, R1_46_1, R1_58_3: 820k; R_0805_2012Metric
R1_12_3, R1_34_3, R1_49_3: 1.1M; R_0805_2012Metric
R1_14_3, R1_19_1, R1_25_1, R1_33_0, R1_47_0, R1_53_0: 360k; R_0805_2012Metric
R1_16_1, R1_16_2, R1_28_0, R1_28_3, R1_30_0, R1_38_3: 220k; R_0805_2012Metric
R1_17_3, R1_32_2, R1_36_2, R1_57_2, R1_60_3: 560k; R_0805_2012Metric
R1_18_3: 910k; R_0805_2012Metric
R1_23_3: 24k; R_0805_2012Metric
R1_26_0, R1_36_3, R1_52_1, R1_52_3, R1_59_1: 750k; R_0805_2012Metric
R1_26_3, R1_57_1: 1.5M; R_0805_2012Metric
R1_27_1, R1_33_2, R1_40_1, R1_51_0, R1_61_0: 120k; R_0805_2012Metric
R1_27_3, R1_51_2: 2M; R_0805_2012Metric
R1_28_1, R1_34_1, R1_44_1, R1_50_0, R1_58_0, R1_62_3: 180k; R_0805_2012Metric
R1_29_3, R1_63_0: 62k; R_0805_2012Metric
R1_30_3: 20k; R_0805_2012Metric
R1_31_2, R1_39_2: 68k; R_0805_2012Metric
R1_31_3: 43k; R_0805_2012Metric
R1_37_1: 620k; R_0805_2012Metric
R1_39_3: 27k; R_0805_2012Metric
R1_51_3: 2.2M; R_0805_2012Metric
R1_56_1: 39k; R_0805_2012Metric
R_BAL_1_4: 14.3k; R_0805_2012Metric
R_BAL_1_5: 10k; R_0805_2012Metric
R_BAL_1_6: 13k; R_0805_2012Metric
R_BAL_1_7: 16.2k; R_0805_2012Metric
Rb_N4, Rb_N5: 330k; R_0805_2012Metric
Rb_N6: 1.1M; R_0805_2012Metric
Rb_N7: 390k; R_0805_2012Metric
Rf_N4, Rf_N5, Rf_N6, Rf_N7: 100k; R_0805_2012Metric
U1: TL074; SOIC-14_3.9x8.7mm_P1.27mm

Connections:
+5V_REF: J_STRADDLE_EDGE.B35, Rb_N4.1, Rb_N5.1, Rb_N6.1, Rb_N7.1
+15V: C_U1P.2, J_STRADDLE_EDGE.B33, J_STRADDLE_EDGE.B34, U1.4
-15V: C_U1N.1, J_STRADDLE_EDGE.B37, J_STRADDLE_EDGE.B38, U1.11
GND: C_U1N.2, C_U1P.1, H1.1, H2.1, J_STRADDLE_EDGE.A37, J_STRADDLE_EDGE.A38, R_BAL_1_4.2, R_BAL_1_5.2, R_BAL_1_6.2, R_BAL_1_7.2
INV_N4: R1_0_0.2, R1_1_0.2, R1_2_0.2, R1_4_0.2, R1_5_0.2, R1_6_0.2, R1_8_0.2, R1_10_0.2, R1_11_0.2, R1_12_0.2, R1_15_0.2, R1_18_0.2, R1_21_0.2, R1_22_0.2, R1_24_0.2, R1_25_0.2, R1_26_0.2, R1_30_0.2, R1_31_0.2, R1_47_0.2, R1_48_0.2, R1_49_0.2, R1_50_0.2, R1_51_0.2, R1_52_0.2, R1_53_0.2, R1_54_0.2, R1_55_0.2, R1_57_0.2, R1_58_0.2, R1_59_0.2, R1_60_0.2, R1_61_0.2, R1_63_0.2, Rb_N4.2, Rf_N4.1, U1.2
INV_N5: R1_1_1.2, R1_2_1.2, R1_3_1.2, R1_4_1.2, R1_5_1.2, R1_6_1.2, R1_7_1.2, R1_10_1.2, R1_11_1.2, R1_15_1.2, R1_16_1.2, R1_17_1.2, R1_19_1.2, R1_20_1.2, R1_22_1.2, R1_23_1.2, R1_26_1.2, R1_27_1.2, R1_28_1.2, R1_29_1.2, R1_35_1.2, R1_36_1.2, R1_39_1.2, R1_47_1.2, R1_48_1.2, R1_54_1.2, R1_55_1.2, R1_56_1.2, R1_57_1.2, R1_58_1.2, R1_61_1.2, R1_63_1.2, Rb_N5.2, Rf_N5.1, U1.6
INV_N6: R1_0_2.2, R1_1_2.2, R1_4_2.2, R1_5_2.2, R1_6_2.2, R1_7_2.2, R1_8_2.2, R1_9_2.2, R1_10_2.2, R1_11_2.2, R1_12_2.2, R1_13_2.2, R1_14_2.2, R1_15_2.2, R1_28_2.2, R1_29_2.2, R1_35_2.2, R1_36_2.2, R1_37_2.2, R1_38_2.2, R1_39_2.2, R1_40_2.2, R1_45_2.2, R1_46_2.2, R1_47_2.2, R1_50_2.2, R1_51_2.2, R1_54_2.2, R1_58_2.2, R1_59_2.2, R1_60_2.2, R1_61_2.2, Rf_N6.1, U1.9
INV_N7: R1_12_3.2, R1_13_3.2, R1_14_3.2, R1_15_3.2, R1_21_3.2, R1_22_3.2, R1_23_3.2, R1_24_3.2, R1_25_3.2, R1_26_3.2, R1_27_3.2, R1_32_3.2, R1_34_3.2, R1_35_3.2, R1_36_3.2, R1_37_3.2, R1_40_3.2, R1_43_3.2, R1_44_3.2, R1_45_3.2, R1_49_3.2, R1_51_3.2, R1_52_3.2, R1_57_3.2, R1_58_3.2, R1_59_3.2, R1_60_3.2, R1_62_3.2, R1_63_3.2, R_BAL_1_7.1, Rb_N7.2, Rf_N7.1, U1.13
IN_0: J_STRADDLE_EDGE.A1, R1_0_0.1, R1_0_1.1, R1_0_2.1, R1_0_3.1
IN_1: J_STRADDLE_EDGE.A2, R1_1_0.1, R1_1_1.1, R1_1_2.1, R1_1_3.1
IN_2: J_STRADDLE_EDGE.A3, R1_2_0.1, R1_2_1.1, R1_2_3.1
IN_3: J_STRADDLE_EDGE.A4, R1_3_0.1, R1_3_1.1, R1_3_2.1, R1_3_3.1
IN_4: J_STRADDLE_EDGE.A5, R1_4_0.1, R1_4_1.1, R1_4_2.1, R1_4_3.1
IN_5: J_STRADDLE_EDGE.A6, R1_5_0.1, R1_5_1.1, R1_5_2.1, R1_5_3.1
IN_6: J_STRADDLE_EDGE.A7, R1_6_0.1, R1_6_1.1, R1_6_2.1, R1_6_3.1
IN_7: J_STRADDLE_EDGE.A8, R1_7_1.1, R1_7_2.1, R1_7_3.1
IN_8: J_STRADDLE_EDGE.A9, R1_8_0.1, R1_8_1.1, R1_8_2.1, R1_8_3.1
IN_9: J_STRADDLE_EDGE.A10, R1_9_0.1, R1_9_2.1
IN_10: J_STRADDLE_EDGE.A11, R1_10_0.1, R1_10_1.1, R1_10_2.1
IN_11: J_STRADDLE_EDGE.A12, R1_11_0.1, R1_11_1.1, R1_11_2.1
IN_12: J_STRADDLE_EDGE.A13, R1_12_0.1, R1_12_2.1, R1_12_3.1
IN_13: J_STRADDLE_EDGE.A14, R1_13_2.1, R1_13_3.1
IN_14: J_STRADDLE_EDGE.A15, R1_14_0.1, R1_14_1.1, R1_14_2.1, R1_14_3.1
IN_15: J_STRADDLE_EDGE.A16, R1_15_0.1, R1_15_1.1, R1_15_2.1, R1_15_3.1
IN_16: J_STRADDLE_EDGE.A17, R1_16_1.1, R1_16_2.1, R1_16_3.1
IN_17: J_STRADDLE_EDGE.A18, R1_17_1.1, R1_17_3.1
IN_18: J_STRADDLE_EDGE.A19, R1_18_0.1, R1_18_3.1
IN_19: J_STRADDLE_EDGE.A20, R1_19_1.1, R1_19_2.1
IN_20: J_STRADDLE_EDGE.A21, R1_20_0.1, R1_20_1.1, R1_20_2.1
IN_21: J_STRADDLE_EDGE.A22, R1_21_0.1, R1_21_2.1, R1_21_3.1
IN_22: J_STRADDLE_EDGE.A23, R1_22_0.1, R1_22_1.1, R1_22_2.1, R1_22_3.1
IN_23: J_STRADDLE_EDGE.A24, R1_23_1.1, R1_23_2.1, R1_23_3.1
IN_24: J_STRADDLE_EDGE.A25, R1_24_0.1, R1_24_1.1, R1_24_3.1
IN_25: J_STRADDLE_EDGE.A26, R1_25_0.1, R1_25_1.1, R1_25_3.1
IN_26: J_STRADDLE_EDGE.A27, R1_26_0.1, R1_26_1.1, R1_26_3.1
IN_27: J_STRADDLE_EDGE.A28, R1_27_0.1, R1_27_1.1, R1_27_3.1
IN_28: J_STRADDLE_EDGE.A29, R1_28_0.1, R1_28_1.1, R1_28_2.1, R1_28_3.1
IN_29: J_STRADDLE_EDGE.A30, R1_29_0.1, R1_29_1.1, R1_29_2.1, R1_29_3.1
IN_30: J_STRADDLE_EDGE.A31, R1_30_0.1, R1_30_1.1, R1_30_2.1, R1_30_3.1
IN_31: J_STRADDLE_EDGE.A32, R1_31_0.1, R1_31_1.1, R1_31_2.1, R1_31_3.1
IN_32: J_STRADDLE_EDGE.B1, R1_32_0.1, R1_32_1.1, R1_32_2.1, R1_32_3.1
IN_33: J_STRADDLE_EDGE.B2, R1_33_0.1, R1_33_1.1, R1_33_2.1, R1_33_3.1
IN_34: J_STRADDLE_EDGE.B3, R1_34_0.1, R1_34_1.1, R1_34_2.1, R1_34_3.1
IN_35: J_STRADDLE_EDGE.B4, R1_35_0.1, R1_35_1.1, R1_35_2.1, R1_35_3.1
IN_36: J_STRADDLE_EDGE.B5, R1_36_0.1, R1_36_1.1, R1_36_2.1, R1_36_3.1
IN_37: J_STRADDLE_EDGE.B6, R1_37_0.1, R1_37_1.1, R1_37_2.1, R1_37_3.1
IN_38: J_STRADDLE_EDGE.B7, R1_38_0.1, R1_38_1.1, R1_38_2.1, R1_38_3.1
IN_39: J_STRADDLE_EDGE.B8, R1_39_0.1, R1_39_1.1, R1_39_2.1, R1_39_3.1
IN_40: J_STRADDLE_EDGE.B9, R1_40_0.1, R1_40_1.1, R1_40_2.1, R1_40_3.1
IN_41: J_STRADDLE_EDGE.B10, R1_41_0.1, R1_41_1.1, R1_41_2.1
IN_42: J_STRADDLE_EDGE.B11, R1_42_0.1, R1_42_1.1, R1_42_2.1, R1_42_3.1
IN_43: J_STRADDLE_EDGE.B12, R1_43_0.1, R1_43_1.1, R1_43_2.1, R1_43_3.1
IN_44: J_STRADDLE_EDGE.B13, R1_44_0.1, R1_44_1.1, R1_44_2.1, R1_44_3.1
IN_45: J_STRADDLE_EDGE.B14, R1_45_0.1, R1_45_1.1, R1_45_2.1, R1_45_3.1
IN_46: J_STRADDLE_EDGE.B15, R1_46_0.1, R1_46_1.1, R1_46_2.1, R1_46_3.1
IN_47: J_STRADDLE_EDGE.B16, R1_47_0.1, R1_47_1.1, R1_47_2.1, R1_47_3.1
IN_48: J_STRADDLE_EDGE.B17, R1_48_0.1, R1_48_1.1, R1_48_2.1
IN_49: J_STRADDLE_EDGE.B18, R1_49_0.1, R1_49_2.1, R1_49_3.1
IN_50: J_STRADDLE_EDGE.B19, R1_50_0.1, R1_50_2.1
IN_51: J_STRADDLE_EDGE.B20, R1_51_0.1, R1_51_1.1, R1_51_2.1, R1_51_3.1
IN_52: J_STRADDLE_EDGE.B21, R1_52_0.1, R1_52_1.1, R1_52_3.1
IN_53: J_STRADDLE_EDGE.B22, R1_53_0.1, R1_53_2.1
IN_54: J_STRADDLE_EDGE.B23, R1_54_0.1, R1_54_1.1, R1_54_2.1
IN_55: J_STRADDLE_EDGE.B24, R1_55_0.1, R1_55_1.1, R1_55_3.1
IN_56: J_STRADDLE_EDGE.B25, R1_56_1.1, R1_56_2.1
IN_57: J_STRADDLE_EDGE.B26, R1_57_0.1, R1_57_1.1, R1_57_2.1, R1_57_3.1
IN_58: J_STRADDLE_EDGE.B27, R1_58_0.1, R1_58_1.1, R1_58_2.1, R1_58_3.1
IN_59: J_STRADDLE_EDGE.B28, R1_59_0.1, R1_59_1.1, R1_59_2.1, R1_59_3.1
IN_60: J_STRADDLE_EDGE.B29, R1_60_0.1, R1_60_1.1, R1_60_2.1, R1_60_3.1
IN_61: J_STRADDLE_EDGE.B30, R1_61_0.1, R1_61_1.1, R1_61_2.1
IN_62: J_STRADDLE_EDGE.B31, R1_62_1.1, R1_62_2.1, R1_62_3.1
IN_63: J_STRADDLE_EDGE.B32, R1_63_0.1, R1_63_1.1, R1_63_3.1
POS_N4: R1_3_0.2, R1_9_0.2, R1_14_0.2, R1_20_0.2, R1_27_0.2, R1_28_0.2, R1_29_0.2, R1_32_0.2, R1_33_0.2, R1_34_0.2, R1_35_0.2, R1_36_0.2, R1_37_0.2, R1_38_0.2, R1_39_0.2, R1_40_0.2, R1_41_0.2, R1_42_0.2, R1_43_0.2, R1_44_0.2, R1_45_0.2, R1_46_0.2, R_BAL_1_4.1, U1.3
POS_N5: R1_0_1.2, R1_8_1.2, R1_14_1.2, R1_24_1.2, R1_25_1.2, R1_30_1.2, R1_31_1.2, R1_32_1.2, R1_33_1.2, R1_34_1.2, R1_37_1.2, R1_38_1.2, R1_40_1.2, R1_41_1.2, R1_42_1.2, R1_43_1.2, R1_44_1.2, R1_45_1.2, R1_46_1.2, R1_51_1.2, R1_52_1.2, R1_59_1.2, R1_60_1.2, R1_62_1.2, R_BAL_1_5.1, U1.5
POS_N6: R1_3_2.2, R1_16_2.2, R1_19_2.2, R1_20_2.2, R1_21_2.2, R1_22_2.2, R1_23_2.2, R1_30_2.2, R1_31_2.2, R1_32_2.2, R1_33_2.2, R1_34_2.2, R1_41_2.2, R1_42_2.2, R1_43_2.2, R1_44_2.2, R1_48_2.2, R1_49_2.2, R1_53_2.2, R1_56_2.2, R1_57_2.2, R1_62_2.2, R_BAL_1_6.1, Rb_N6.2, U1.10
POS_N7: R1_0_3.2, R1_1_3.2, R1_2_3.2, R1_3_3.2, R1_4_3.2, R1_5_3.2, R1_6_3.2, R1_7_3.2, R1_8_3.2, R1_16_3.2, R1_17_3.2, R1_18_3.2, R1_28_3.2, R1_29_3.2, R1_30_3.2, R1_31_3.2, R1_33_3.2, R1_38_3.2, R1_39_3.2, R1_42_3.2, R1_46_3.2, R1_47_3.2, R1_55_3.2, U1.12
V_SUM_4: J_STRADDLE_EDGE.A33, Rf_N4.2, U1.1
V_SUM_5: J_STRADDLE_EDGE.A34, Rf_N5.2, U1.7
V_SUM_6: J_STRADDLE_EDGE.A35, Rf_N6.2, U1.8
V_SUM_7: J_STRADDLE_EDGE.A36, Rf_N7.2, U1.14
